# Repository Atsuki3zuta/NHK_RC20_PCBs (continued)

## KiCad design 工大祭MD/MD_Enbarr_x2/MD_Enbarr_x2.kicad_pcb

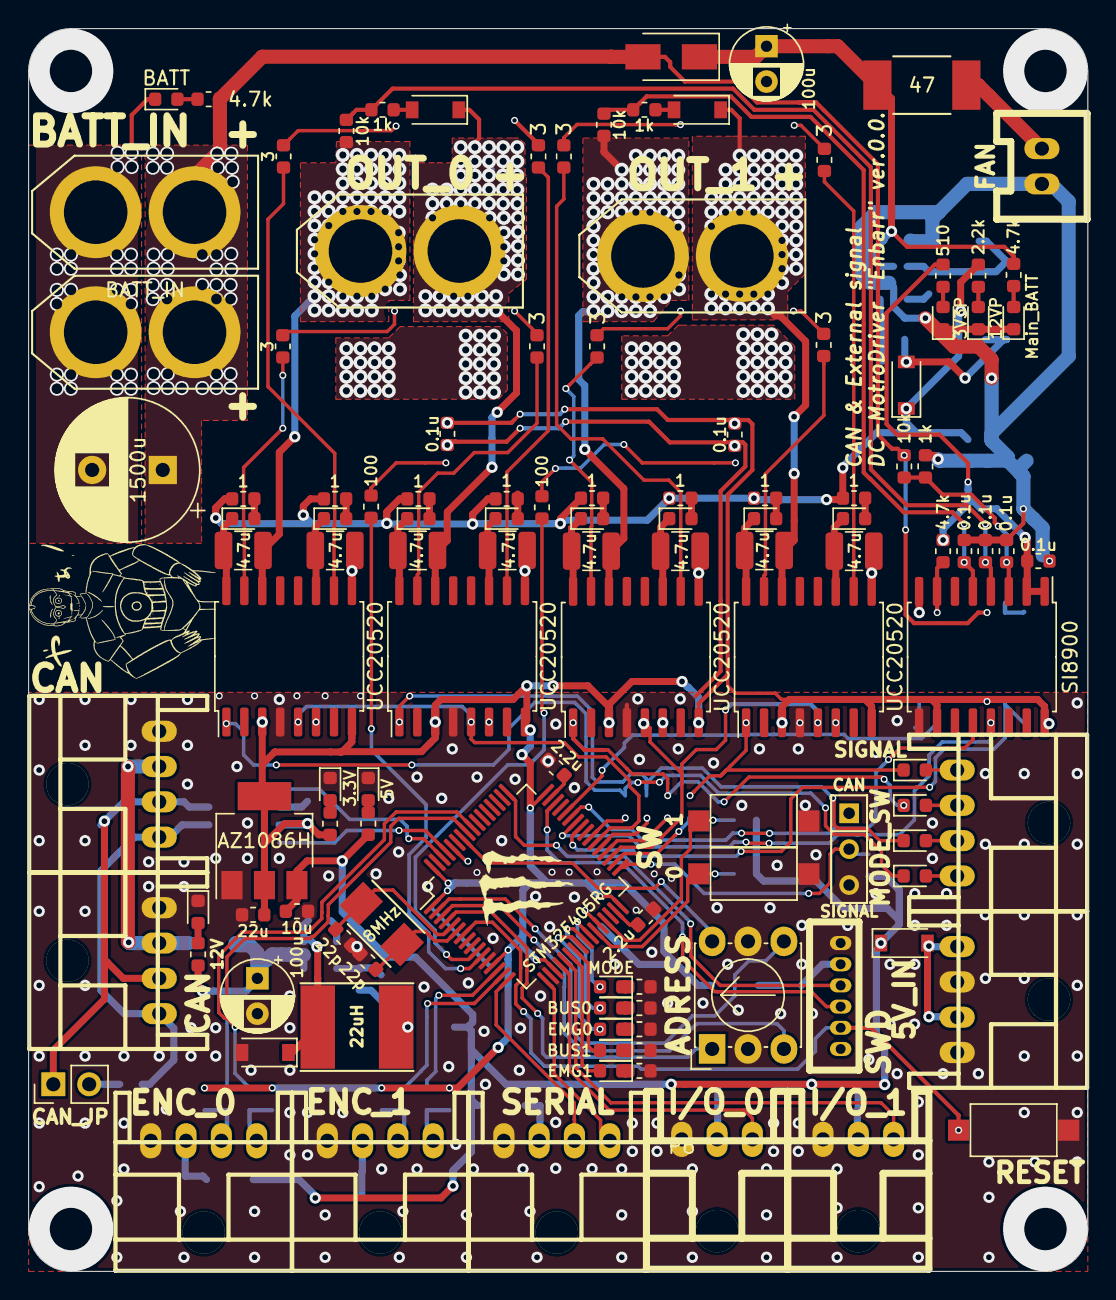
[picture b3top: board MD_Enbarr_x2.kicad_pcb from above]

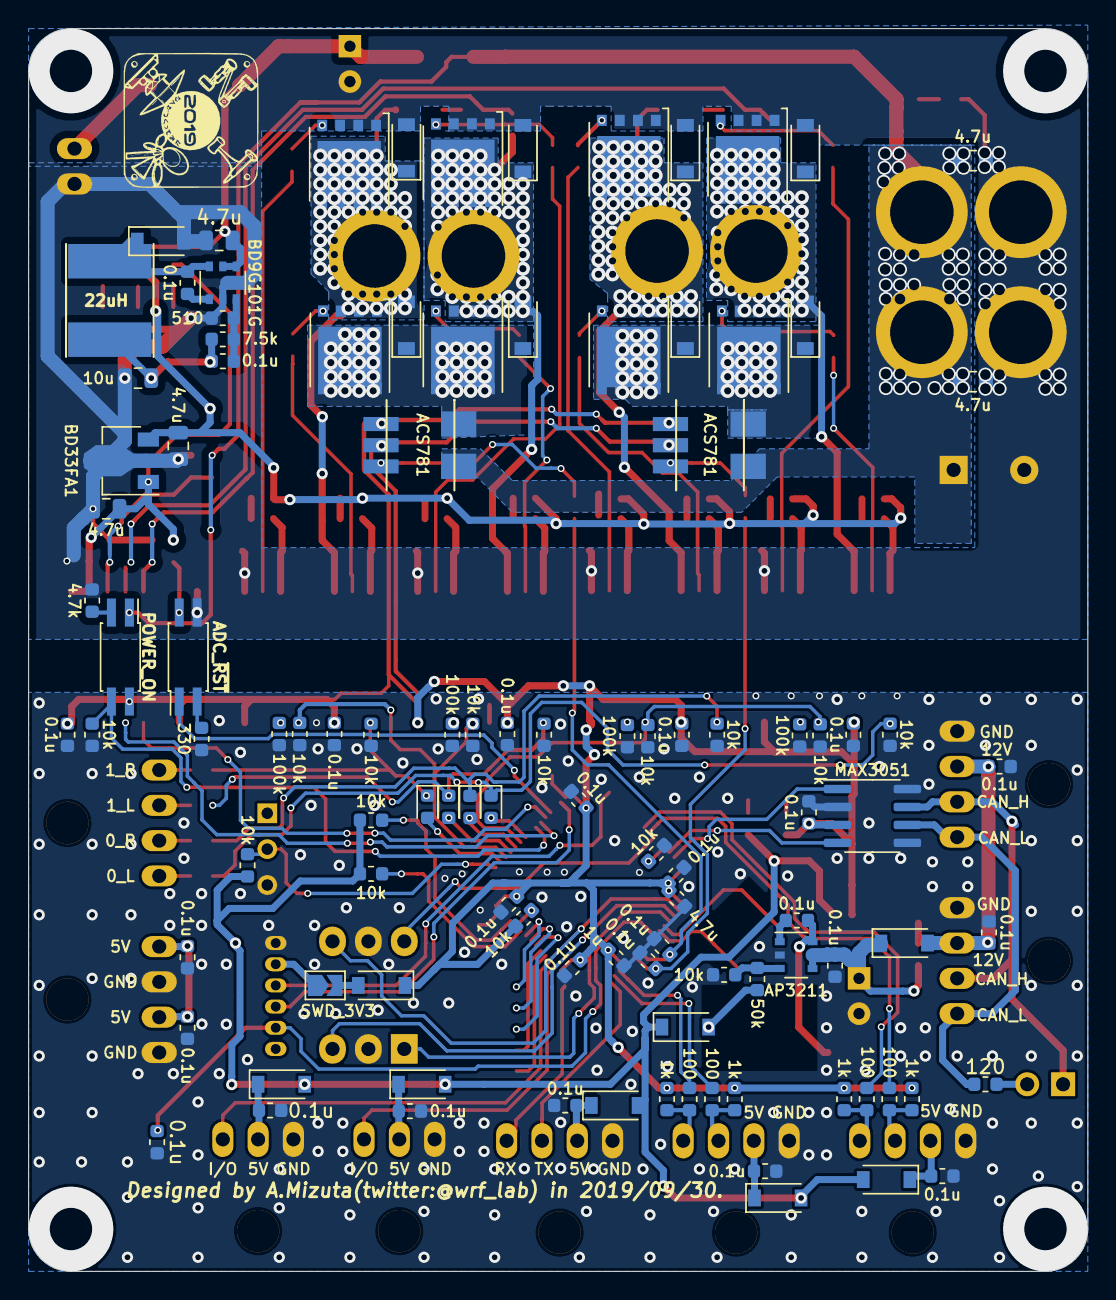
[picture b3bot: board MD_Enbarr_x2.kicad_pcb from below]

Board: 2 copper layers, 75.0 x 88.0 mm, 230 parts (107 on the bottom side), 149 nets.

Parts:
C1, C3: 22p; C_0603_1608Metric
C2, C4, C5, C6, C7, C8, C9, C11, C15, C16, C17, C18, C21, C22, C23, C24, C26, C27, C36, C38, C39, C40, C41, C42, C44, C45, C46, C49, C50, C51, C54, C55: 0.1u; C_0603_1608Metric
C10: 1u; C_0603_1608Metric
C12: 4.7u; C_0603_1608Metric
C13, C14: 2.2u; C_0603_1608Metric
C19, C20, C30, C31, C47, C48, C52, C53: 4.7u; C_1210_3225Metric
C25, C33: 100u; CP_Radial_D5.0mm_P2.50mm
C28: 10u; C_0805_2012Metric
C29, C32, C35, C37, C43: 4.7u; C_0805_2012Metric
C34: 1500u; CP_Radial_D10.0mm_P5.00mm
C56: 10u; C_0603_1608Metric
C57: 22u; C_0603_1608Metric
D1, D4, D5, D6, D10, D16, D17, D18, D24, D25, D26, D28, D29, D30, D31, D38, D45, D46, D47, D48, D49, D52: DIODE; D_SOD-123
D2, D3, D12, D13, D14, D19, D20, D35, D36, D37, D41, D42, D43, D44, D50, D51: DIODE; D_0603_1608Metric
D7: EMG1; LED_0603_1608Metric
D8: BUS1; LED_0603_1608Metric
D9: EMG0; LED_0603_1608Metric
D15: DIODE; D_SMA
D21: BATT; LED_0603_1608Metric
D22: 12VP; LED_0603_1608Metric
D23: 3V3P; LED_0603_1608Metric
D27: Main_BATT; LED_0603_1608Metric
D32: 12V; LED_0603_1608Metric
D33: 5V; LED_0603_1608Metric
D34: 3.3V; LED_0603_1608Metric
D39: BUS0; LED_0603_1608Metric
D40: MODE; LED_0603_1608Metric
JP1: SWD_3V3; SolderJumper-2_P1.3mm_Open_TrianglePad1.0x1.5mm
JP2: CAN_JP; PinHeader_1x02_P2.54mm_Vertical
L1, L2: 22uH; Inductor_Taiyo-Yuden_NR-60xx_HandSoldering
P1: SWD; ZH_6P
P2: 5V_IN; XA_4LC
P3, P4: CAN; XA_4LC
P5: SERIAL; XA_4LC
P6: I/O_0; XA_3LC
P7: FAN; XA_2P
P8: BATT_IN; XT60_M
P9: BATT_IN; XT60_F
P10: OUT_1; XT60_F
P11: ENC_0; XA_4LC
P12: SIGNAL; XA_4LC
P13: ENC_1; XA_4LC
P14: I/O_1; XA_3LC
P15: OUT_0; XT60_F
Q1, Q2, Q3, Q4, Q5, Q6, Q7, Q8: BSC014N06; TDSON-8-1
R1, R2, R4, R5, R9, R10, R22, R26, R36, R38, R39, R53, R61, R68, R69, R70, R71, R72: 10k; R_0603_1608Metric
R3: 120; R_0603_1608Metric
R6, R7, R8, R12, R49, R51, R52: 330; R_0603_1608Metric
R11, R35, R54, R67: 100k; R_0603_1608Metric
R14: 7.5k; R_0603_1608Metric
R15, R34, R48: 510; R_0603_1608Metric
R16, R32, R40, R41: 4.7k; R_0603_1608Metric
R17, R18, R30, R31, R55, R56, R65, R66: 3; R_0603_1608Metric
R19, R20, R28, R29, R58, R59, R63, R64: 1; R_0603_1608Metric
R21, R23, R24, R27, R42, R43, R62: 1k; R_0603_1608Metric
R25: 47; R_2812
R33: 2.2k; R_0603_1608Metric
R37: 50k; R_0603_1608Metric
R44, R45, R46, R50, R57, R60: 100; R_0603_1608Metric
R47: 1.2k; R_0603_1608Metric
SW1: RESET; SW_SPST_CK_RS282G05A3
SW2: MODE_SW; SW_Micro_SPST
SW3: SW0; SW_SPST_CK_RS282G05A3
SW4: SW1; SW_SPST_CK_RS282G05A3
SW5: ADRESS; Nidec_Copal_SH-7010C
U1: MAX3051; SOIC-8_3.9x4.9mm_P1.27mm
U2: AP3211; TSOP-6_1.65x3.05mm_P0.95mm
U3: STM32F405RG; LQFP-64_10x10mm_P0.5mm
U4, U8, U10, U14: UCC20520; SOIC-16W_7.5x10.3mm_P1.27mm
U5: SI8900; SOIC-16W_7.5x10.3mm_P1.27mm
U6: ADC_~RST; SO-4_4.4x2.3mm_P1.27mm
U7: BD9G101G; TSOP-6_1.65x3.05mm_P0.95mm
U9: BD33FA1; SOT-89-3
U11: POWER_ON; SO-4_4.4x2.3mm_P1.27mm
U12, U13: ACS781; ACS781_No_side_mask
U15: AZ1086H; SOT-223-3_TabPin2
U16: LOGO; Mini_Monster
U17: LOGO; C3PO_silk_11.3x15.0
U18: LOGO; NT_2019_Logo_10.0x10.0_Silk
Y1: 8MHz; Crystal_SMD_5032_2Pads

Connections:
+3.3VP: C22.1, C32.1, R16.1, R34.2, U5.1, U5.2, U9.1
+3V3: C5.1, C6.1, C8.1, C9.1, C10.1, C12.1, C17.1, C36.1, C40.1, C41.1, C42.1, C45.1, C46.1, C54.1, C57.1, D4.1, R9.1, R21.1, R24.1, R42.1, R43.1, R49.2, U1.3, U3.1, U3.13, U3.19, U3.32, U3.48, U3.64, U4.3, U4.8, U5.10, U5.16, U8.3, U8.8, U10.3, U10.8, U11.4, U12.1, U13.1, U14.3, U14.8, U15.2
+5V: C56.1, D1.1, D6.2, D10.2, D26.1, D28.2, D38.2, D52.2, R2.1, R4.1, R5.1, R48.2, U15.3
+12P: C29.1, D18.1, R19.1, R20.1, R28.1, R29.1, R33.2, R58.1, R59.1, R63.1, R64.1, U9.3
+12V: C33.1, C38.1, D5.1, R47.2, U2.4, U2.5
+BATT: C34.1, C35.1, C43.1, D15.2, P8.2, P9.2, R22.1, R32.2, U11.1, U12.5, U13.5
/ADC_~RST: R16.2, U5.7, U6.4
/ADR_1: SW5.1, U3.4
/ADR_2: SW5.2, U3.2
/ADR_4: SW5.4, U3.3
/ADR_8: SW5.8, U3.58
/CAN1_RX: U1.4, U3.61
/CAN1_TX: U1.1, U3.62
/CAN_H: JP2.1, P3.3, P4.3, U1.7
/CAN_L: P3.4, P4.4, R3.1, U1.6
/CAN_Vdd: C7.2, C11.2, D5.2, P3.2, P4.2
/CounterVoltage0: C27.1, R26.2, R27.1, U5.4
/CounterVoltage1: C51.1, R61.2, R62.1, U5.5
/Current0: C50.1, R60.2, U3.11
/Current1: C49.1, R57.2, U3.10
/EN0: R10.1, R36.1, U3.38, U4.5, U10.5
/EN1: R53.1, R68.1, U3.35, U8.5, U14.5
/FB: R37.2, R38.1, U2.3
/FB_PWR: C18.2, R14.2, R15.1, U7.3
/FB_PWR_OUT: C18.1, C28.1, D18.2, L1.2, R14.1
/LED0: D7.2, U3.22
/LED1: D8.2, U3.23
/LED2: D9.2, U3.24
/LED3: D39.2, U3.25
/LED4: D40.2, U3.26
/MODE: R2.2, SW2.2, U3.33
/MOTOR0_BATT: D25.1, D30.1, Q1.5, Q3.5, U13.6
/MOTOR1_BATT: D45.1, D48.1, Q5.5, Q7.5, U12.6
/OSC_IN: C1.2, U3.5, Y1.1
/OSC_OUT: C3.2, U3.6, Y1.2
/OUT0_L: C19.2, D25.2, D29.1, P15.1, Q1.1, Q1.2, Q1.3, Q2.5, R26.1, U4.14
/OUT0_R: C30.2, D17.1, D30.2, D31.1, P15.2, Q3.1, Q3.2, Q3.3, Q4.5, U10.14
/OUT1_L: C47.2, D45.2, D46.1, P10.1, Q5.1, Q5.2, Q5.3, Q6.5, R61.1, U8.14
/OUT1_R: C52.2, D47.1, D48.2, D49.1, P10.2, Q7.1, Q7.2, Q7.3, Q8.5, U14.14
/PA4: P6.3, U3.20
/PA5: P14.3, U3.21
/PA8: R39.1, U3.41, U11.3
/PA11: U3.44, U6.1
/PWM0_L: D2.1, D37.1, R69.1, U4.1
/PWM0_R: D3.1, D36.1, R71.1, U10.1
/PWM1_L: D12.1, D42.1, R70.1, U8.1
/PWM1_R: D35.1, D41.1, R72.1, U14.1
/SW0: R4.2, SW3.2, U3.27
/SW1: R5.2, SW4.2, U3.29
/SWCLK: P1.3, U3.49
/SWDIO: P1.4, U3.46
/TIM3_CH1: R44.2, U3.56
/TIM3_CH2: R45.2, U3.57
/TIM5_CH1: R46.2, U3.14
/TIM5_CH2: R50.2, U3.15
/USART1_RX: U3.43, U5.12
/USART1_TX: U3.42, U5.13
/USART2_RX: P5.4, U3.17
/USART2_TX: P5.3, U3.16
/Voltage: C24.1, R22.2, R23.1, U5.3
/batt: C25.1, C37.1, D15.1, R25.2, R41.2, U7.4, U7.5
/~RST: C2.2, P1.5, SW1.1, U3.7
GND: C1.1, C2.1, C3.1, C4.1, C5.2, C6.2, C7.1, C8.2, C9.2, C10.2, C11.1, C12.2, C13.2, C14.2, C15.1, C16.1, C17.2, C21.1, C26.1, C33.2, C36.2, C38.2, C40.2, C41.2, C42.2, C44.1, C45.2, C46.2, C49.2, C50.2, C54.2, C55.1, C56.2, C57.2, D24.2, D32.1, D33.1, D34.1, P1.1, P2.1, P2.3, P3.1, P4.1, P5.1, P6.1, P11.1, P13.1, P14.1, R1.2, R6.2, R7.2, R8.2, R10.2, R11.2, R12.2, R35.2, R36.2, R38.2, R39.2, R51.2, R52.2, R53.2, R54.2, R67.2, R68.2, R69.2, R70.2, R71.2, R72.2, SW1.2, SW2.3, SW3.1, SW4.1, SW5.C, U1.2, U1.5, U1.8, U2.2, U3.12, U3.18, U3.63, U4.4, U5.9, U8.4, U10.4, U12.2, U13.2, U14.4, U15.1
GNDPWR: C20.2, C22.2, C24.2, C25.2, C27.2, C28.2, C29.2, C31.2, C32.2, C34.2, C35.2, C37.2, C43.2, C48.2, C51.2, C53.2, D16.2, D21.1, D22.1, D23.1, D27.1, D29.2, D31.2, D46.2, D49.2, P7.1, P8.1, P9.1, Q2.1, Q2.2, Q2.3, Q4.1, Q4.2, Q4.3, Q6.1, Q6.2, Q6.3, Q8.1, Q8.2, Q8.3, R15.2, R23.2, R40.2, U4.9, U5.8, U6.3, U7.2, U8.9, U9.2, U10.9, U14.9
unnamed: C13.1, U3.31
unnamed: C14.1, U3.47
unnamed: C15.2, D6.1, P5.2
unnamed: C16.2, D10.1, P6.2
unnamed: C19.1, D13.1, U4.16
unnamed: C20.1, D14.1, U4.11
unnamed: C4.2, C21.2, D1.2, P2.2, P2.4
unnamed: C23.1, D16.1, L1.1, U7.6
unnamed: C23.2, U7.1
unnamed: C26.2, D28.1, P11.2
unnamed: C30.1, D19.1, U10.16
unnamed: C31.1, D20.1, U10.11
unnamed: C39.1, D24.1, L2.1, U2.6
unnamed: C39.2, U2.1
unnamed: C44.2, D38.1, P13.2
unnamed: C47.1, D43.1, U8.16
unnamed: C48.1, D44.1, U8.11
unnamed: C52.1, D50.1, U14.16
unnamed: C53.1, D51.1, U14.11
unnamed: C55.2, D52.1, P14.2
unnamed: D2.2, P12.1
unnamed: D3.2, P12.2
unnamed: D4.2, JP1.2
unnamed: D7.1, R6.1
unnamed: D8.1, R7.1
unnamed: D9.1, R8.1
unnamed: D12.2, P12.3
unnamed: D13.2, R19.2
unnamed: D14.2, R20.2
unnamed: D17.2, R27.2
unnamed: D19.2, R28.2
unnamed: D20.2, R29.2
unnamed: D21.2, R32.1
unnamed: D22.2, R33.1
unnamed: D23.2, R34.1
unnamed: D26.2, L2.2, R37.1
unnamed: D27.2, R41.1
unnamed: D32.2, R47.1
unnamed: D33.2, R48.1
unnamed: D34.2, R49.1
unnamed: D35.2, P12.4
unnamed: D36.2, U3.37
unnamed: D37.2, U3.39
unnamed: D39.1, R51.1
unnamed: D40.1, R52.1
unnamed: D41.2, U3.34
unnamed: D42.2, U3.36
unnamed: D43.2, R58.2
unnamed: D44.2, R59.2
unnamed: D47.2, R62.2
unnamed: D50.2, R63.2
unnamed: D51.2, R64.2
unnamed: JP1.1, P1.2
unnamed: JP2.2, R3.2
unnamed: P7.2, R25.1
unnamed: P11.3, R43.2, R45.1
unnamed: P11.4, R42.2, R44.1
unnamed: P13.3, R24.2, R50.1
unnamed: P13.4, R21.2, R46.1
unnamed: Q1.4, R17.1
unnamed: Q2.4, R18.1
unnamed: Q3.4, R30.1
unnamed: Q4.4, R31.1
unnamed: Q5.4, R55.1
unnamed: Q6.4, R56.1
unnamed: Q7.4, R65.1
unnamed: Q8.4, R66.1
unnamed: R1.1, U3.60
unnamed: R9.2, U3.28
unnamed: R11.1, U4.6
unnamed: R12.1, U6.2
unnamed: R17.2, U4.15
unnamed: R18.2, U4.10
unnamed: R30.2, U10.15
unnamed: R31.2, U10.10
unnamed: R35.1, U10.6
unnamed: R40.1, U11.2
unnamed: R54.1, U8.6
unnamed: R55.2, U8.15
unnamed: R56.2, U8.10
unnamed: R57.1, U12.3
unnamed: R60.1, U13.3
unnamed: R65.2, U14.15
unnamed: R66.2, U14.10
unnamed: R67.1, U14.6
